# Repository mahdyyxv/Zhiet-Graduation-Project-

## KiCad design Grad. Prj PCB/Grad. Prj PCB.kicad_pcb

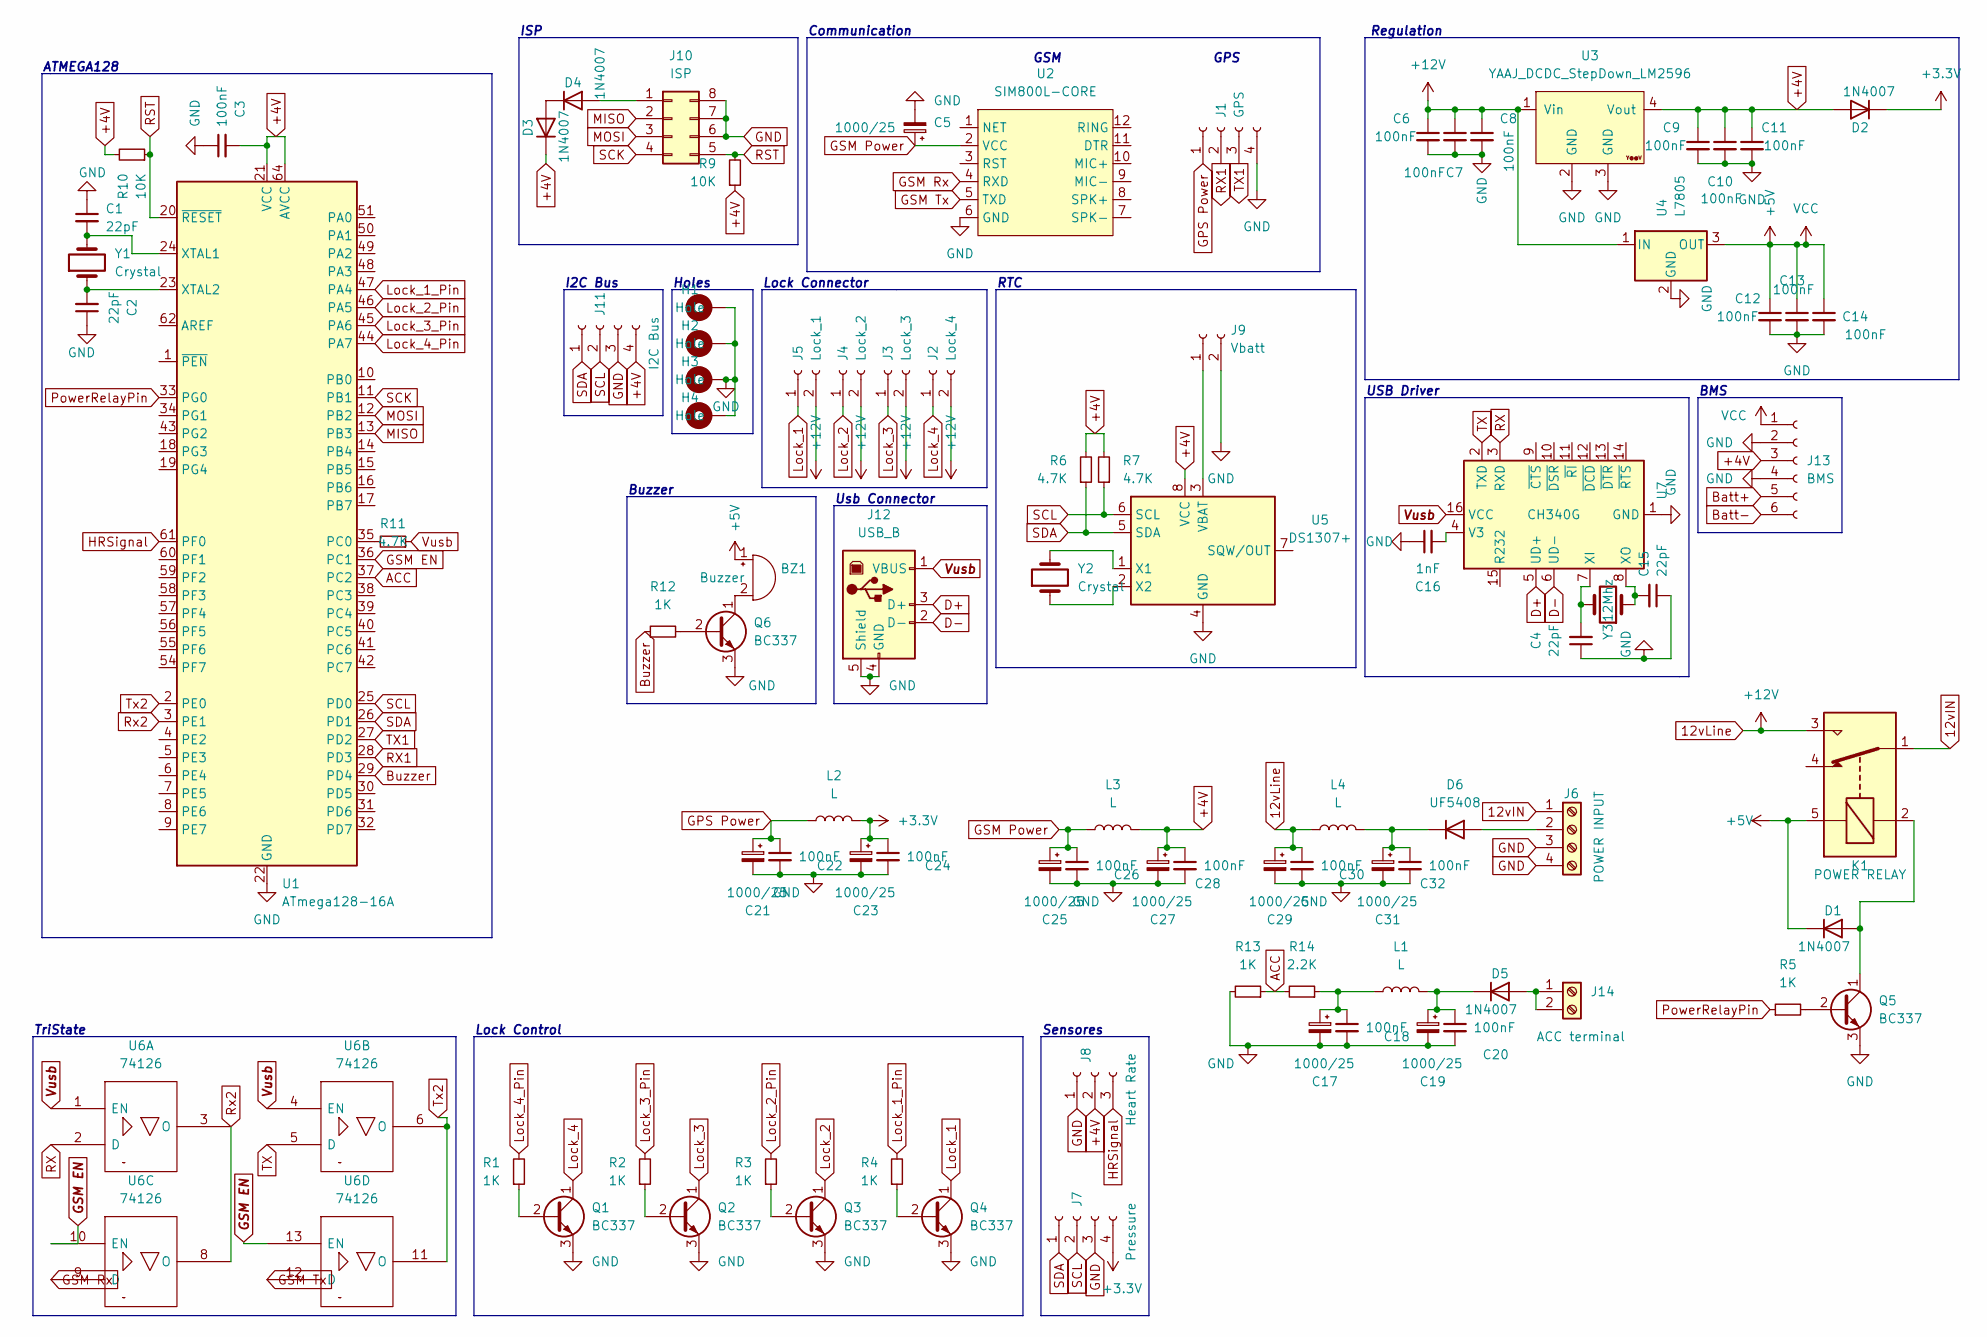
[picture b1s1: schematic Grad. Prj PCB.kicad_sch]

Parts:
BZ1: Buzzer; Buzzer_12x9.5RM7.6
C1, C2: 22pF; C_Disc_D3.0mm_W1.6mm_P2.50mm
C3, C6, C7, C8, C9, C10, C11, C12, C13, C14, C18, C20, C22, C24, C26, C28, C30, C32: 100nF; C_Disc_D4.3mm_W1.9mm_P5.00mm
C4, C15: 22pF; C_Disc_D3.8mm_W2.6mm_P2.50mm
C5, C17, C19, C21, C23, C25, C27, C29, C31: 1000/25; CP_Radial_D8.0mm_P3.80mm
C16: 1nF; C_Disc_D3.8mm_W2.6mm_P2.50mm
D1, D2, D3, D4, D5: 1N4007; D_DO-41_SOD81_P10.16mm_Horizontal
D6: UF5408; D_DO-201AD_P15.24mm_Horizontal
H1, H2, H3: Hole; MountingHole_3.2mm_M3_ISO7380_Pad
H4: Hole
J1: GPS; PinHeader_1x04_P2.54mm_Vertical
J2: Lock_4; Molex_KK-254_AE-6410-02A_1x02_P2.54mm_Vertical
J3: Lock_3; Molex_KK-254_AE-6410-02A_1x02_P2.54mm_Vertical
J4: Lock_2; Molex_KK-254_AE-6410-02A_1x02_P2.54mm_Vertical
J5: Lock_1; Molex_KK-254_AE-6410-02A_1x02_P2.54mm_Vertical
J6: POWER INPUT; Altech_AK300_1x04_P5.00mm_45-Degree
J7: Pressure; PinHeader_1x04_P2.54mm_Vertical
J8: Heart Rate; PinSocket_1x03_P2.54mm_Vertical
J9: Vbatt; Molex_KK-254_AE-6410-02A_1x02_P2.54mm_Vertical
J10: ISP; PinSocket_2x04_P2.54mm_Vertical
J11: I2C Bus; PinHeader_1x04_P2.54mm_Vertical
J12: USB_B; USB_B_OST_USB-B1HSxx_Horizontal
J13: BMS; TP4056-Module
J14: ACC terminal
K1: POWER RELAY; Relay_SPDT_SANYOU_SRD_Series_Form_C
L1, L4: L
L2: L; L_Axial_L6.6mm_D2.7mm_P10.16mm_Horizontal_Vishay_IM-2
L3: L; L_6.3x6.3_H3
Q1, Q2, Q3, Q4, Q5, Q6: BC337; TO-92_Inline
R1, R2, R3, R4, R5, R12, R13: 1K; R_Axial_DIN0207_L6.3mm_D2.5mm_P7.62mm_Horizontal
R6, R7, R11: 4.7K; R_Axial_DIN0207_L6.3mm_D2.5mm_P7.62mm_Horizontal
R9, R10: 10K; R_Axial_DIN0207_L6.3mm_D2.5mm_P7.62mm_Horizontal
R14: 2.2K; R_Axial_DIN0207_L6.3mm_D2.5mm_P7.62mm_Horizontal
U1: ATmega128-16A; TQFP-64_14x14mm_P0.8mm
U2: SIM800L-CORE
U3: YAAJ_DCDC_StepDown_LM2596
U4: L7805; TO-220-3_Vertical
U5: DS1307+; DIP-8_W7.62mm
U6: 74126; DIP-14_W7.62mm_LongPads
U7: CH340G; SOIC-16_3.9x9.9mm_P1.27mm
Y1: Crystal; Crystal_HC49-U_Vertical
Y2: Crystal; Crystal_C26-LF_D2.1mm_L6.5mm_Vertical
Y3: 12Mhz; Crystal_HC49-4H_Vertical

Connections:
12vIN: J6.1, K1.1
12vLine: C6.1, C7.1, C8.1, C29.1, C30.1, J2.2, J3.2, J4.2, J5.2, K1.3, L4.1, U3.1 (Vin), U4.1 (IN)
+3.3V: C23.1, C24.1, D2.1 (K), J7.4, L2.2
+4V: C3.2, C9.1, C10.1, C11.1, C27.1, C28.1, D2.2 (A), D3.1 (K), J8.2, J11.4, J13.3, L3.2, R6.2, R7.2, R9.1, R10.2, U1.21 (VCC), U1.52 (VCC), U1.64 (AVCC), U3.4 (Vout), U5.8 (VCC)
+5V: BZ1.1 (-), C12.1, C13.1, C14.1, D1.1 (K), J13.1, K1.5, U4.3 (OUT), U6.14 (VCC)
ACC: R13.1, R14.2, U1.37 (PC2)
Batt+: J13.5
Batt-: J13.6
Buzzer: R12.1, U1.29 (PD4)
D+: J12.3 (D+), U7.5 (UD+)
D-: J12.2 (D-), U7.6 (UD-)
GND: C1.1, C2.1, C3.1, C4.1, C5.2, C6.2, C7.2, C8.2, C9.2, C10.2, C11.2, C12.2, C13.2, C14.2, C15.1, C16.1, C17.2, C18.2, C19.2, C20.2, C21.2, C22.2, C23.2, C24.2, C25.2, C26.2, C27.2, C28.2, C29.2, C30.2, C31.2, C32.2, H1.1, H2.1, H3.1, H4.1, J1.4, J6.3, J6.4, J7.3, J8.1, J9.2, J10.6, J10.7, J10.8, J11.3, J12.4 (GND), J12.5 (Shield), J13.2, J13.4, Q1.3 (E), Q2.3 (E), Q3.3 (E), Q4.3 (E), Q5.3 (E), Q6.3 (E), R13.2, U1.22 (GND), U1.53 (GND), U1.63 (GND), U2.6 (GND), U3.2 (GND), U3.3 (GND), U4.2 (GND), U5.4 (GND), U6.7 (GND), U7.1 (GND)
GPS Power: C21.1, C22.1, J1.1, L2.1
GSM EN: U1.36 (PC1), U6.10 (EN), U6.13 (EN)
GSM Power: C5.1, C25.1, C26.1, L3.1, U2.2 (VCC)
GSM Rx: U2.4 (RXD), U6.9 (D)
GSM Tx: U2.5 (TXD), U6.12 (D)
HRSignal: J8.3, U1.61 (PF0)
Lock_1: J5.1, Q4.1 (C)
Lock_1_Pin: R4.2, U1.47 (PA4)
Lock_2: J4.1, Q3.1 (C)
Lock_2_Pin: R3.2, U1.46 (PA5)
Lock_3: J3.1, Q2.1 (C)
Lock_3_Pin: R2.2, U1.45 (PA6)
Lock_4: J2.1, Q1.1 (C)
Lock_4_Pin: R1.2, U1.44 (PA7)
MISO: J10.2, U1.13 (PB3)
MOSI: J10.3, U1.12 (PB2)
unnamed: BZ1.2 (+), Q6.1 (C)
unnamed: C1.2, U1.24 (XTAL1), Y1.2
unnamed: C2.2, U1.23 (XTAL2), Y1.1
unnamed: C4.2, U7.7 (XI), Y3.2
unnamed: C15.2, U7.8 (XO), Y3.1
unnamed: C16.2, U7.4 (V3)
unnamed: C19.1, C20.1, D5.1 (K), L1.2
unnamed: C31.1, C32.1, D6.1 (K), L4.2
unnamed: D1.2 (A), K1.2, Q5.1 (C)
unnamed: D3.2 (A), D4.1 (K)
unnamed: D4.2 (A), J10.1
unnamed: D6.2 (A), J6.2
unnamed: D5.2 (A), J14.1, J14.2
unnamed: Q1.2 (B), R1.1
unnamed: Q2.2 (B), R2.1
unnamed: Q3.2 (B), R3.1
unnamed: Q4.2 (B), R4.1
unnamed: Q5.2 (B), R5.2
unnamed: Q6.2 (B), R12.2
unnamed: C17.1, C18.1, L1.1, R14.1
unnamed: R11.2, U1.35 (PC0)
unnamed: U5.1 (X1), Y2.2
unnamed: U5.2 (X2), Y2.1
unnamed: J9.1, U5.3 (VBAT)
PowerRelayPin: R5.1, U1.33 (PG0)
RST: J10.5, R9.2, R10.1, U1.20 (~RESET)
RX: U6.2 (D), U7.3 (RXD)
RX1: J1.2, U1.28 (PD3)
Rx2: U1.3 (PE1), U6.3 (O), U6.8 (O)
SCK: J10.4, U1.11 (PB1)
SCL: J7.2, J11.2, R7.1, U1.25 (PD0), U5.6 (SCL)
SDA: J7.1, J11.1, R6.1, U1.26 (PD1), U5.5 (SDA)
TX: U6.5 (D), U7.2 (TXD)
TX1: J1.3, U1.27 (PD2)
Tx2: U1.2 (PE0), U6.6 (O), U6.11 (O)
Vusb: J12.1 (VBUS), R11.1, U6.1 (EN), U6.4 (EN), U7.16 (VCC)

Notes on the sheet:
I2C Bus
Regulation
RTC
USB Driver
GPS
Communication
Buzzer
TriState
ISP
Usb Connector
Holes
Sensores
BMS
GSM
ATMEGA128
Lock Control
Lock Connector

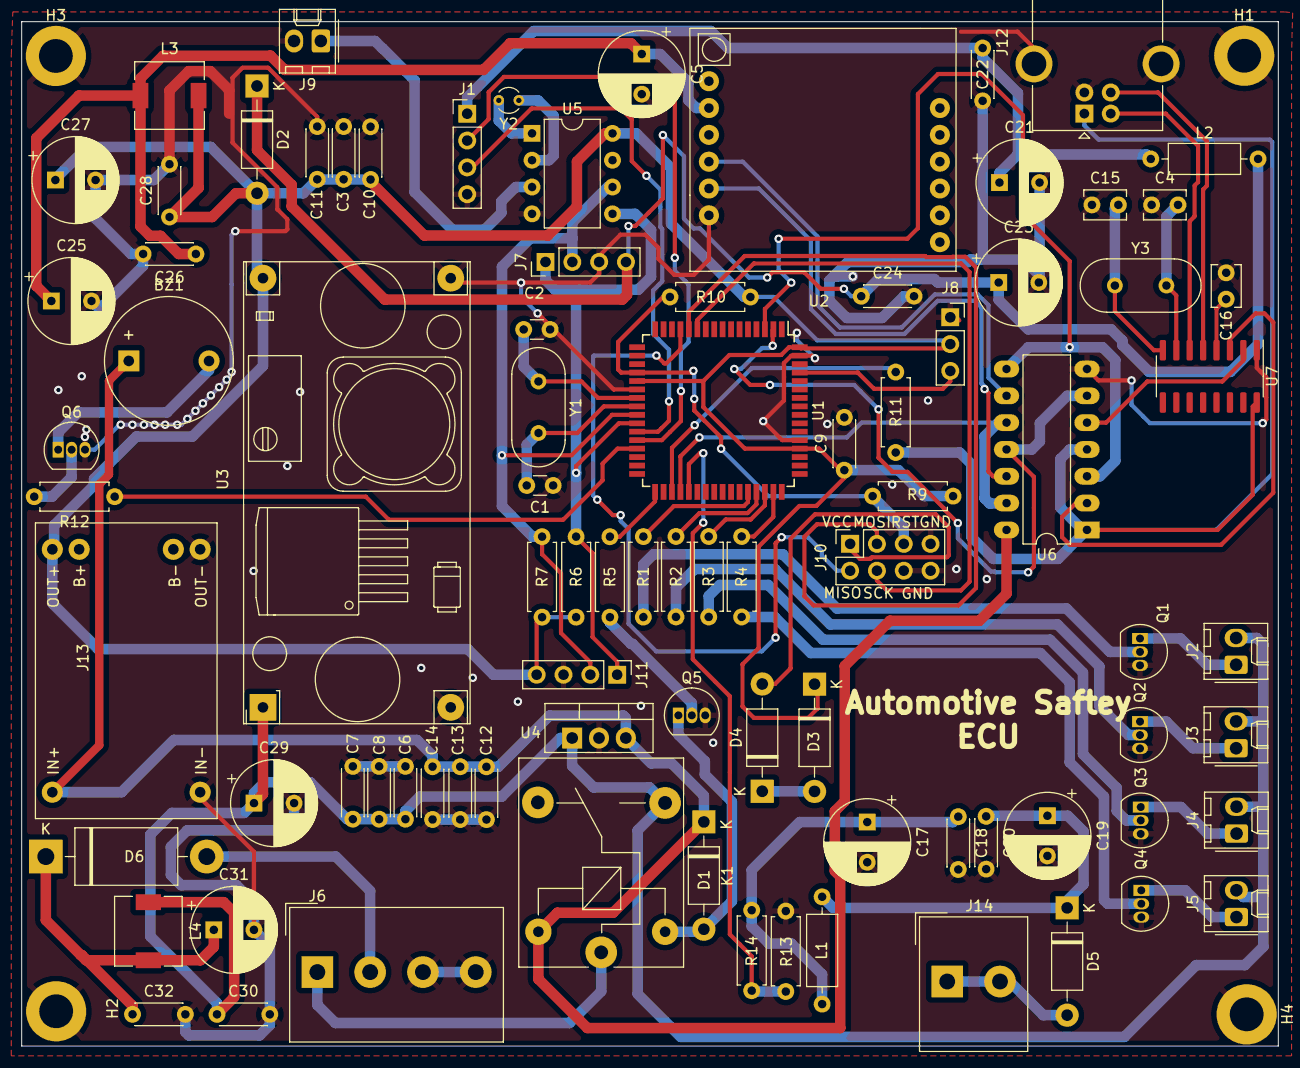
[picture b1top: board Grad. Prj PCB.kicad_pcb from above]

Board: 2 copper layers, 119.0 x 97.0 mm, 91 parts (0 on the bottom side), 62 nets.

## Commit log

2022-10-23 first add
2022-10-23 Added RTC
2022-10-24 Added ISP Pin Header
2022-10-24 Added ISP Header
2022-10-31 Add Lpf and Acc Line in Sch and Brd
2022-10-31 just creat Firware Folder
